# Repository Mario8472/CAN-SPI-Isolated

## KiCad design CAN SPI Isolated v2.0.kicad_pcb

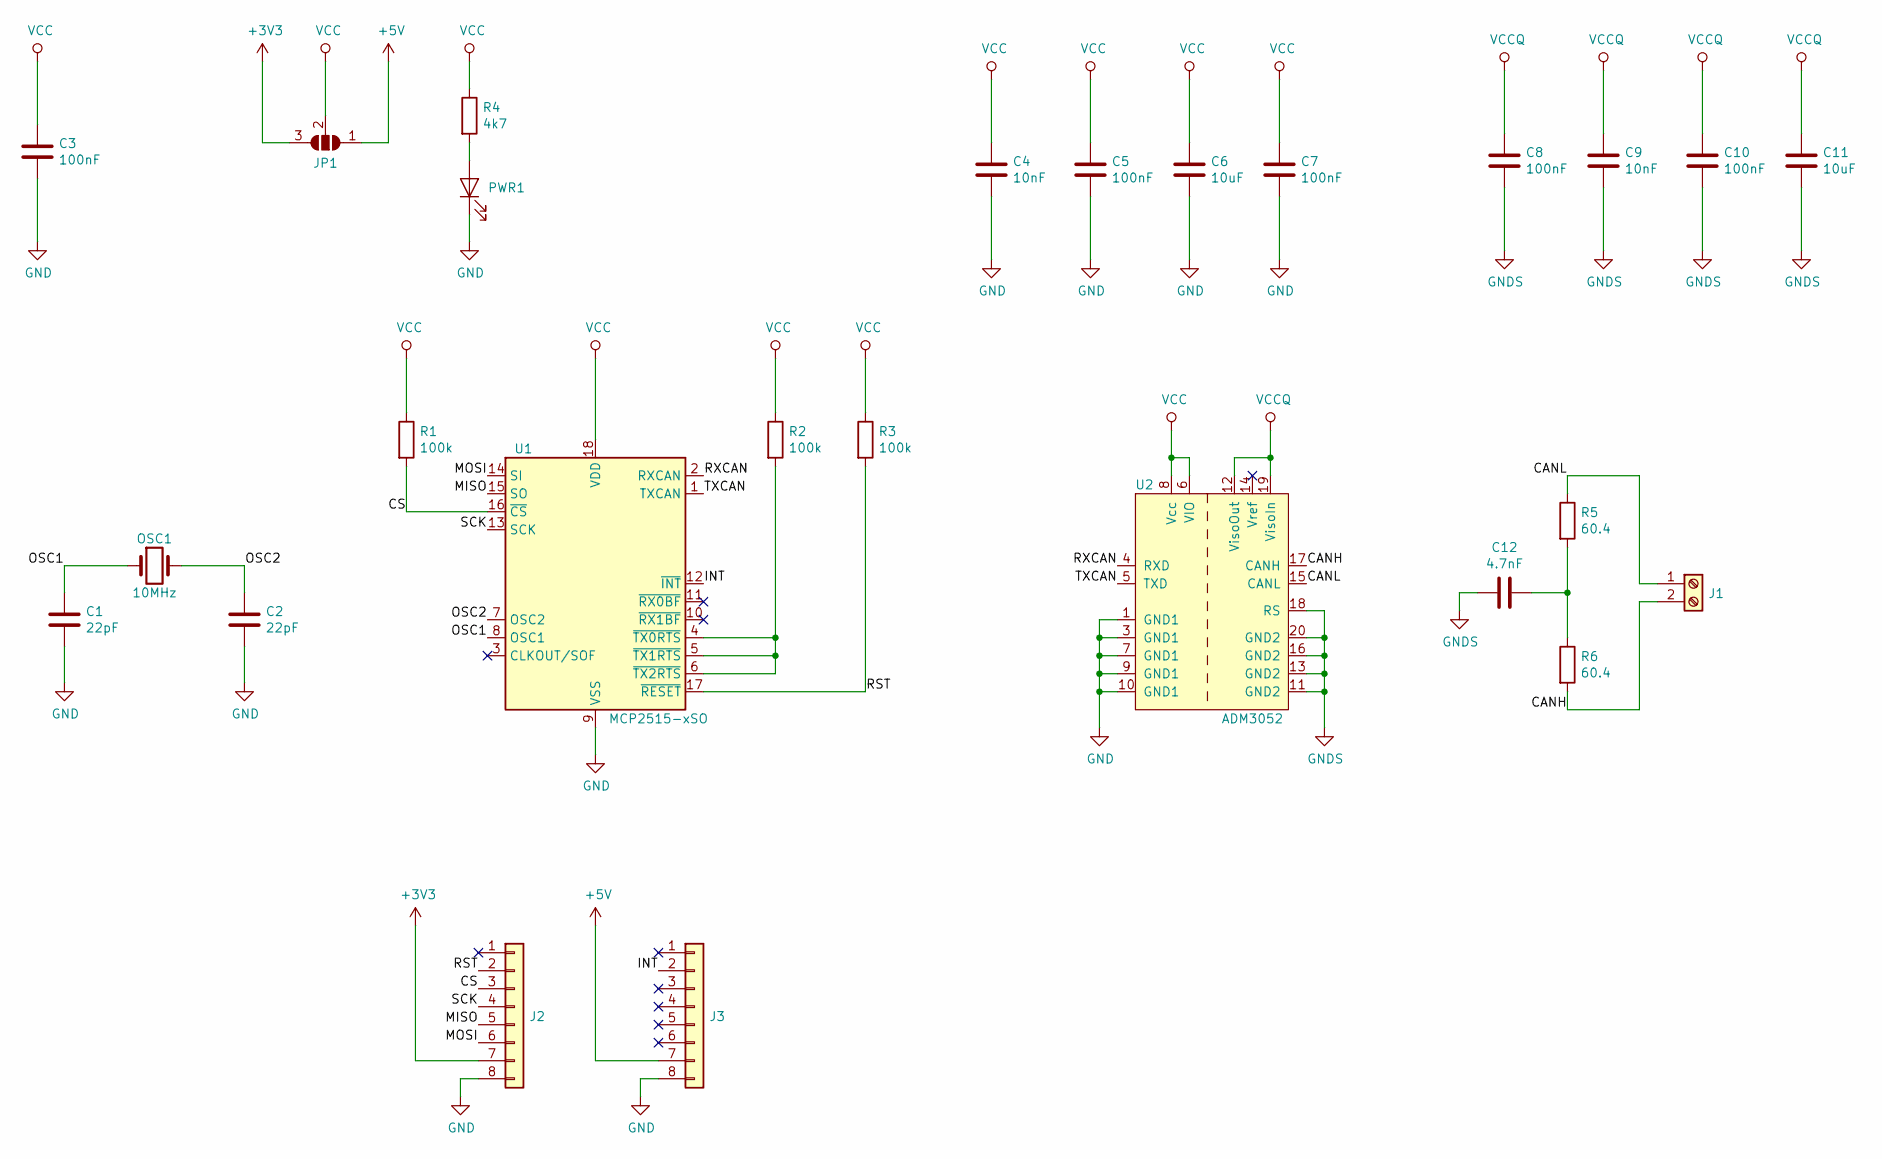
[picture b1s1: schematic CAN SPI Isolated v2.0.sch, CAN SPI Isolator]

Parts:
C1, C2: 22pF; C_0805_2012Metric
C3, C5, C7, C8, C10: 100nF; C_0805_2012Metric
C4, C9: 10nF; C_0805_2012Metric
C6, C11: 10uF; C_0805_2012Metric
C12: 4.7nF; C_0805_2012Metric
J1: Screw_Terminal_01x02; PCB_Screw_Terminal_5.08_2ways
J2, J3: Conn_01x08; PinHeader_1x08_P2.54mm_Vertical
JP1: SolderJumper_3_Open; Jumper_0805
OSC1: 10MHz; Crystal_SMD_HC49-SD
PWR1: LED; LED_0805_2012Metric
R1, R2, R3: 100k; R_0805_2012Metric
R4: 4k7; R_0805_2012Metric
R5, R6: 60.4; R_0805_2012Metric
U1: MCP2515-xSO; SOIC-18W_7.5x11.6mm_P1.27mm
U2: ADM3052; SOIC-20W_7.5x12.8mm_P1.27mm

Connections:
+3V3: J2.7, JP1.3 (B)
+5V: J3.7, JP1.1 (A)
/CANH: J1.2, R6.2, U2.17 (CANH)
/CANL: J1.1, R5.1, U2.15 (CANL)
/CS: J2.3, R1.2, U1.16 (~CS)
/INT: J3.2, U1.12 (~INT)
/MISO: J2.5, U1.15 (SO)
/MOSI: J2.6, U1.14 (SI)
/OSC1: C1.1, OSC1.1, U1.8 (OSC1)
/OSC2: C2.1, OSC1.2, U1.7 (OSC2)
/RST: J2.2, R3.2, U1.17 (~RESET)
/RXCAN: U1.2 (RXCAN), U2.4 (RXD)
/SCK: J2.4, U1.13 (SCK)
/TXCAN: U1.1 (TXCAN), U2.5 (TXD)
GND: C1.2, C2.2, C3.2, C4.2, C5.2, C6.2, C7.2, J2.8, J3.8, PWR1.1 (K), U1.9 (VSS), U2.1 (GND1), U2.3 (GND1), U2.7 (GND1), U2.9 (GND1), U2.10 (GND1)
GNDS: C8.2, C9.2, C10.2, C11.2, C12.1, U2.11 (GND2), U2.13 (GND2), U2.16 (GND2), U2.18 (RS), U2.20 (GND2)
unnamed: C12.2, R5.2, R6.1
unnamed: PWR1.2 (A), R4.2
unnamed: R2.2, U1.4 (~TX0RTS), U1.5 (~TX1RTS), U1.6 (~TX2RTS)
VCC: C3.1, C4.1, C5.1, C6.1, C7.1, JP1.2 (C), R1.1, R2.1, R3.1, R4.1, U1.18 (VDD), U2.6 (VIO), U2.8 (Vcc)
VCCQ: C8.1, C9.1, C10.1, C11.1, U2.12 (VisoOut), U2.19 (VisoIn)

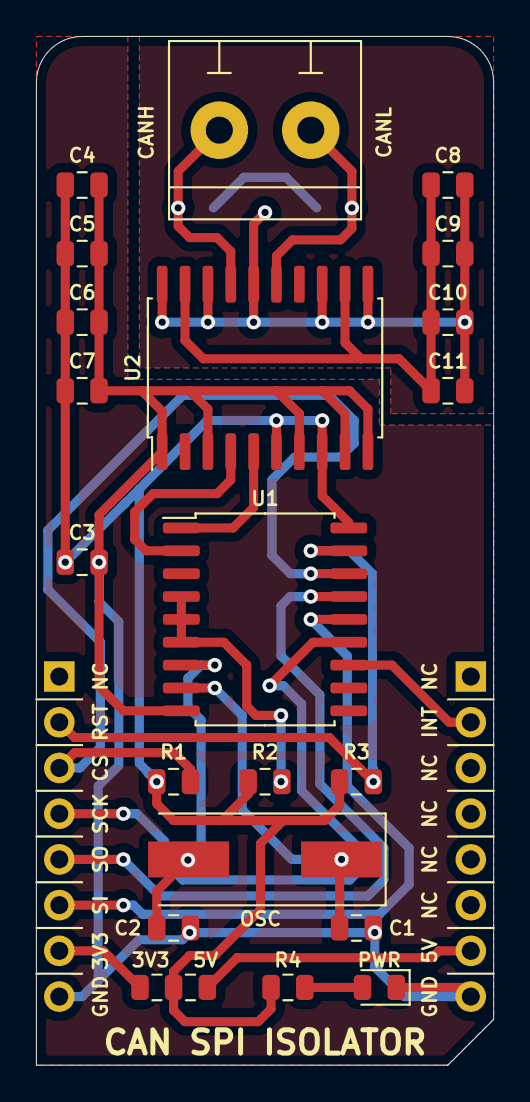
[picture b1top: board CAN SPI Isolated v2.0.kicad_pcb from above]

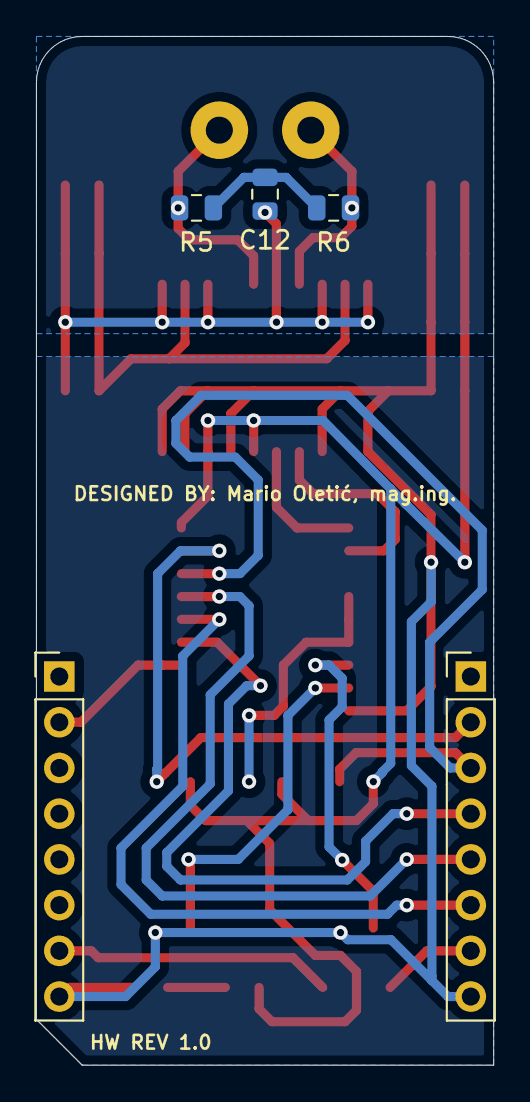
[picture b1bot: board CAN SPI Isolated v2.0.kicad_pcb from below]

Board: 2 copper layers, 25.4 x 57.2 mm, 26 parts (5 on the bottom side), 21 nets.
